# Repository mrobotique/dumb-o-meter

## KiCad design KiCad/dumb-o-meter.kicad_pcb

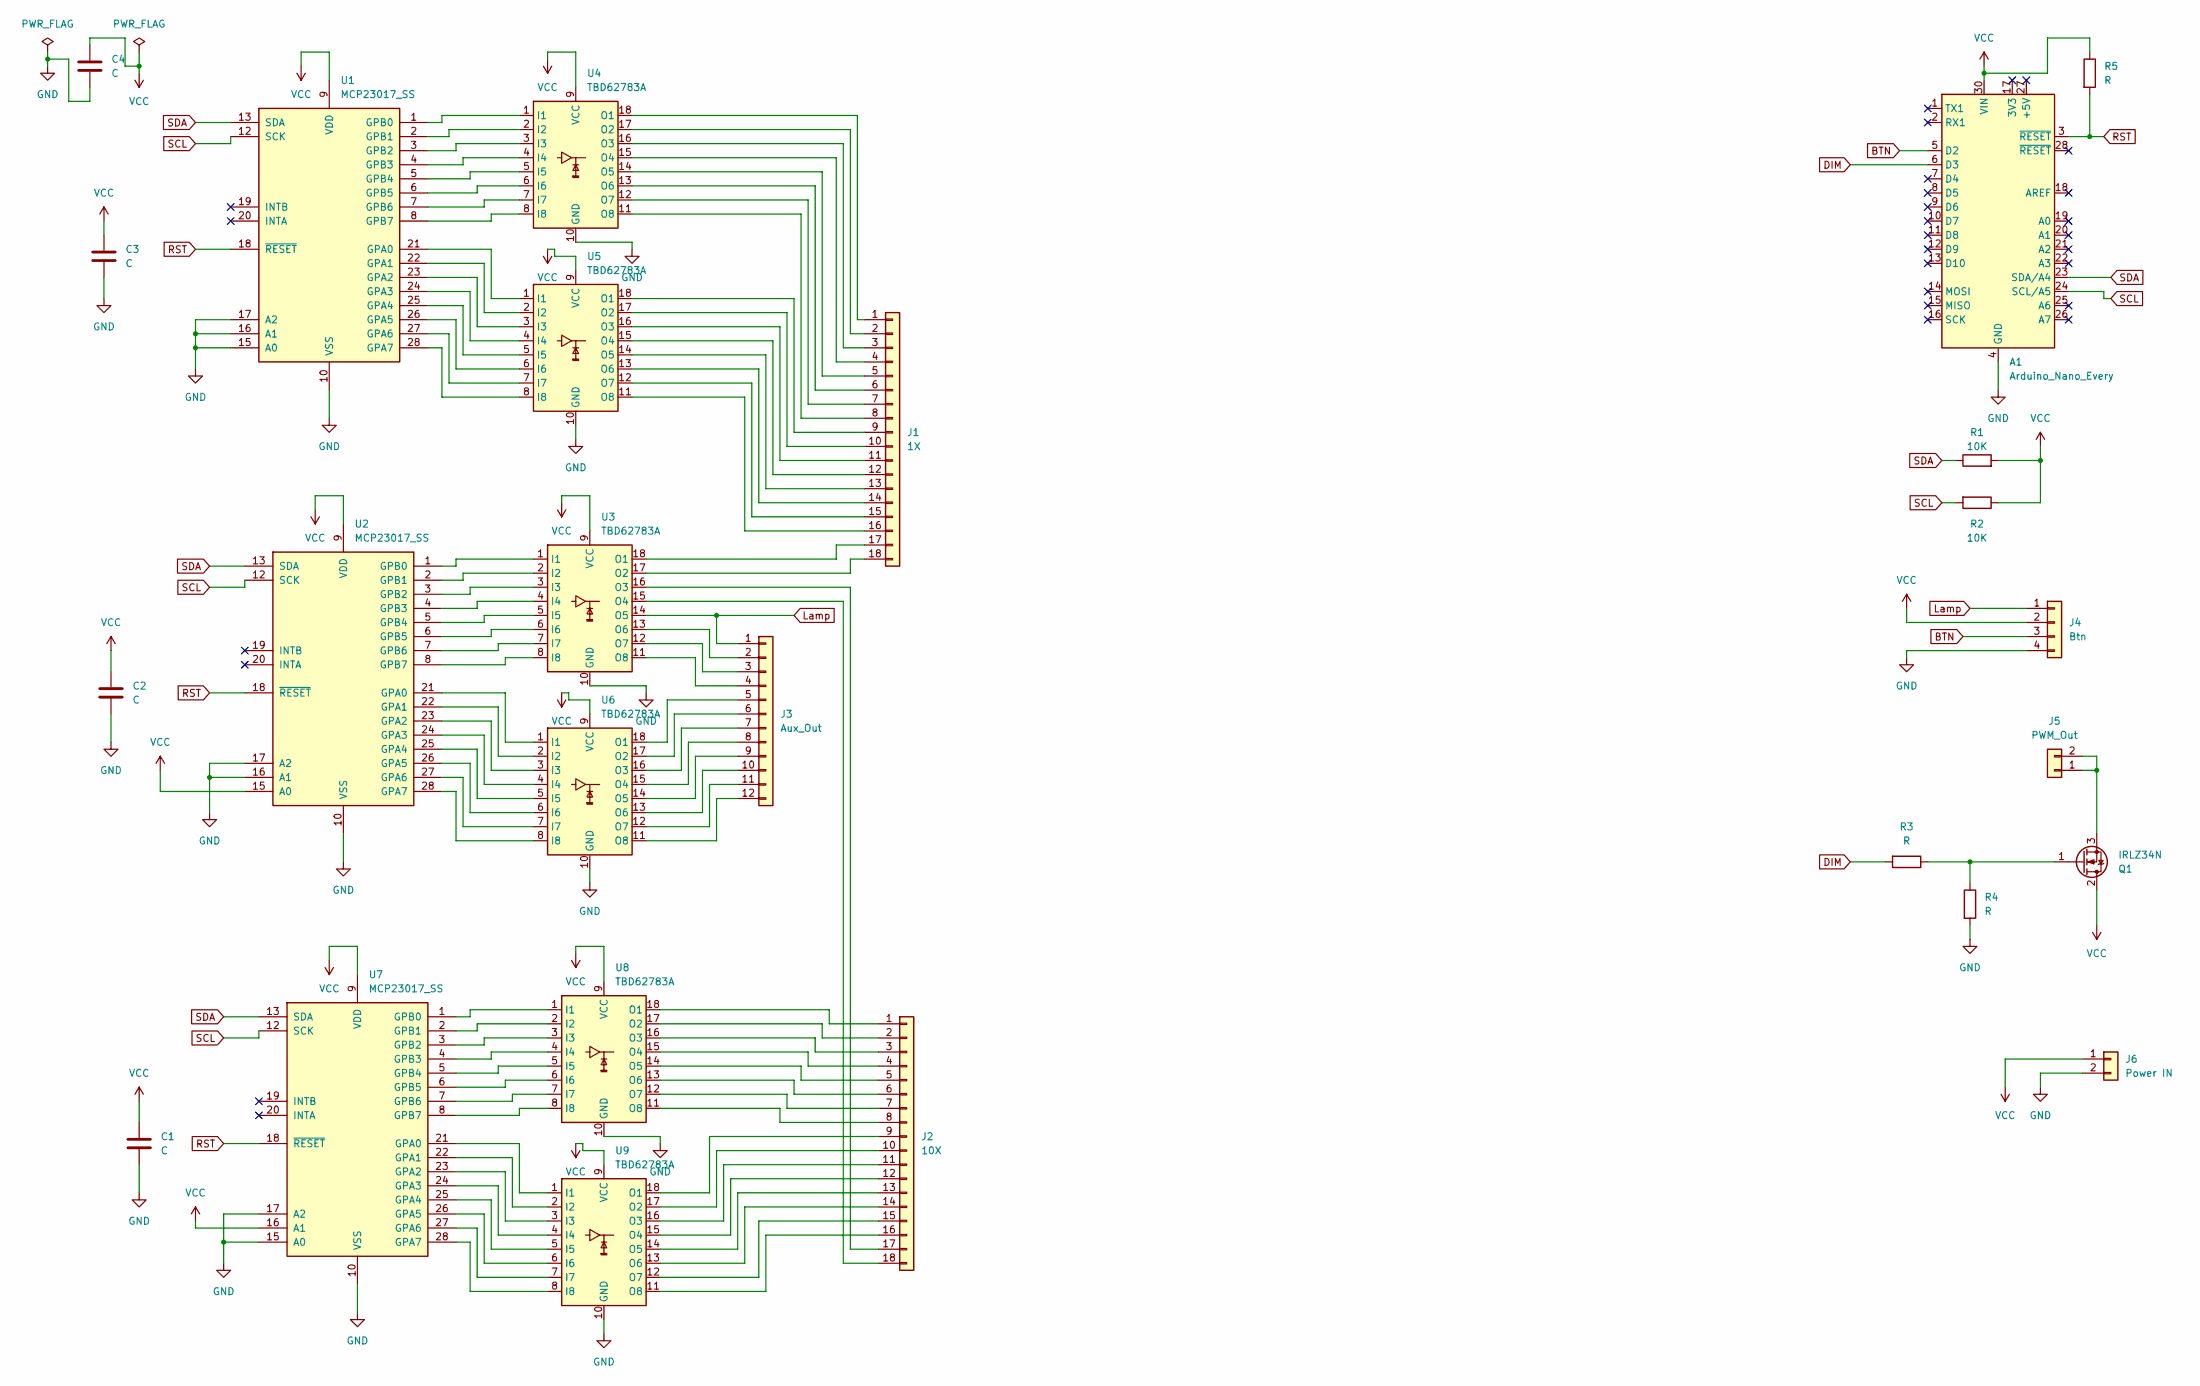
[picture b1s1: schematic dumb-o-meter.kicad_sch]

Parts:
A1: Arduino_Nano_Every; Arduino_Nano
C1, C2, C3: C; C_01005_0402Metric_Pad0.57x0.30mm_HandSolder
C4: C; CP_EIA-7343-15_Kemet-W_Pad2.25x2.55mm_HandSolder
J1: 1X; Wago_734-178_1x18_P3.50mm_Horizontal
J2: 10X; Wago_734-178_1x18_P3.50mm_Horizontal
J3: Aux_Out; PinHeader_1x12_P2.54mm_Vertical
J4: Btn; PinHeader_1x04_P2.54mm_Vertical
J5: PWM_Out; Wago_734-132_1x02_P3.50mm_Vertical
J6: Power IN; Wago_734-132_1x02_P3.50mm_Vertical
Q1: IRLZ34N; TO-263-3_TabPin2
R1, R2: 10K; R_0805_2012Metric_Pad1.20x1.40mm_HandSolder
R3, R4, R5: R; R_0805_2012Metric_Pad1.20x1.40mm_HandSolder
U1, U2, U7: MCP23017_SS; SSOP-28_5.3x10.2mm_P0.65mm
U3, U4, U5, U6, U8, U9: TBD62783A; SOIC-18W_7.5x11.6mm_P1.27mm

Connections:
BTN: A1.5 (D2), J4.3
DIM: A1.6 (D3), R3.2
GND: A1.4 (GND), A1.29 (GND), C1.2, C2.2, C3.2, C4.2, J4.4, J6.2, R4.2, U1.10 (VSS), U1.15 (A0), U1.16 (A1), U1.17 (A2), U2.10 (VSS), U2.16 (A1), U2.17 (A2), U3.10 (GND), U4.10 (GND), U5.10 (GND), U6.10 (GND), U7.10 (VSS), U7.15 (A0), U7.17 (A2), U8.10 (GND), U9.10 (GND)
Lamp: J3.1, J4.1, U3.14 (O5)
unnamed: J1.1, U4.18 (O1)
unnamed: J1.2, U4.17 (O2)
unnamed: J1.3, U4.16 (O3)
unnamed: J1.4, U4.15 (O4)
unnamed: J1.5, U4.14 (O5)
unnamed: J1.6, U4.13 (O6)
unnamed: J1.7, U4.12 (O7)
unnamed: J1.8, U4.11 (O8)
unnamed: J1.9, U5.18 (O1)
unnamed: J1.10, U5.17 (O2)
unnamed: J1.11, U5.16 (O3)
unnamed: J1.12, U5.15 (O4)
unnamed: J1.13, U5.14 (O5)
unnamed: J1.14, U5.13 (O6)
unnamed: J1.15, U5.12 (O7)
unnamed: J1.16, U5.11 (O8)
unnamed: J1.17, U3.18 (O1)
unnamed: J1.18, U3.17 (O2)
unnamed: J2.1, U8.18 (O1)
unnamed: J2.2, U8.17 (O2)
unnamed: J2.3, U8.16 (O3)
unnamed: J2.4, U8.15 (O4)
unnamed: J2.5, U8.14 (O5)
unnamed: J2.6, U8.13 (O6)
unnamed: J2.7, U8.12 (O7)
unnamed: J2.8, U8.11 (O8)
unnamed: J2.9, U9.18 (O1)
unnamed: J2.10, U9.17 (O2)
unnamed: J2.11, U9.16 (O3)
unnamed: J2.12, U9.15 (O4)
unnamed: J2.13, U9.14 (O5)
unnamed: J2.14, U9.13 (O6)
unnamed: J2.15, U9.12 (O7)
unnamed: J2.16, U9.11 (O8)
unnamed: J2.17, U3.16 (O3)
unnamed: J2.18, U3.15 (O4)
unnamed: J3.2, U3.13 (O6)
unnamed: J3.3, U3.12 (O7)
unnamed: J3.4, U3.11 (O8)
unnamed: J3.5, U6.18 (O1)
unnamed: J3.6, U6.17 (O2)
unnamed: J3.7, U6.16 (O3)
unnamed: J3.8, U6.15 (O4)
unnamed: J3.9, U6.14 (O5)
unnamed: J3.10, U6.13 (O6)
unnamed: J3.11, U6.12 (O7)
unnamed: J3.12, U6.11 (O8)
unnamed: J5.1, J5.2, Q1.3 (S)
unnamed: Q1.1 (G), R3.1, R4.1
unnamed: U1.21 (GPA0), U5.1 (I1)
unnamed: U1.22 (GPA1), U5.2 (I2)
unnamed: U1.23 (GPA2), U5.3 (I3)
unnamed: U1.24 (GPA3), U5.4 (I4)
unnamed: U1.25 (GPA4), U5.5 (I5)
unnamed: U1.26 (GPA5), U5.6 (I6)
unnamed: U1.27 (GPA6), U5.7 (I7)
unnamed: U1.28 (GPA7), U5.8 (I8)
unnamed: U1.1 (GPB0), U4.1 (I1)
unnamed: U1.2 (GPB1), U4.2 (I2)
unnamed: U1.3 (GPB2), U4.3 (I3)
unnamed: U1.4 (GPB3), U4.4 (I4)
unnamed: U1.5 (GPB4), U4.5 (I5)
unnamed: U1.6 (GPB5), U4.6 (I6)
unnamed: U1.7 (GPB6), U4.7 (I7)
unnamed: U1.8 (GPB7), U4.8 (I8)
unnamed: U2.21 (GPA0), U6.1 (I1)
unnamed: U2.22 (GPA1), U6.2 (I2)
unnamed: U2.23 (GPA2), U6.3 (I3)
unnamed: U2.24 (GPA3), U6.4 (I4)
unnamed: U2.25 (GPA4), U6.5 (I5)
unnamed: U2.26 (GPA5), U6.6 (I6)
unnamed: U2.27 (GPA6), U6.7 (I7)
unnamed: U2.28 (GPA7), U6.8 (I8)
unnamed: U2.1 (GPB0), U3.1 (I1)
unnamed: U2.2 (GPB1), U3.2 (I2)
unnamed: U2.3 (GPB2), U3.3 (I3)
unnamed: U2.4 (GPB3), U3.4 (I4)
unnamed: U2.5 (GPB4), U3.5 (I5)
unnamed: U2.6 (GPB5), U3.6 (I6)
unnamed: U2.7 (GPB6), U3.7 (I7)
unnamed: U2.8 (GPB7), U3.8 (I8)
unnamed: U7.21 (GPA0), U9.1 (I1)
unnamed: U7.22 (GPA1), U9.2 (I2)
unnamed: U7.23 (GPA2), U9.3 (I3)
unnamed: U7.24 (GPA3), U9.4 (I4)
unnamed: U7.25 (GPA4), U9.5 (I5)
unnamed: U7.26 (GPA5), U9.6 (I6)
unnamed: U7.27 (GPA6), U9.7 (I7)
unnamed: U7.28 (GPA7), U9.8 (I8)
unnamed: U7.1 (GPB0), U8.1 (I1)
unnamed: U7.2 (GPB1), U8.2 (I2)
unnamed: U7.3 (GPB2), U8.3 (I3)
unnamed: U7.4 (GPB3), U8.4 (I4)
unnamed: U7.5 (GPB4), U8.5 (I5)
unnamed: U7.6 (GPB5), U8.6 (I6)
unnamed: U7.7 (GPB6), U8.7 (I7)
unnamed: U7.8 (GPB7), U8.8 (I8)
RST: A1.3 (~RESET), R5.2, U1.18 (~RESET), U2.18 (~RESET), U7.18 (~RESET)
SCL: A1.24 (SCL/A5), R2.2, U1.12 (SCK), U2.12 (SCK), U7.12 (SCK)
SDA: A1.23 (SDA/A4), R1.1, U1.13 (SDA), U2.13 (SDA), U7.13 (SDA)
VCC: A1.30 (VIN), C1.1, C2.1, C3.1, C4.1, J4.2, J6.1, Q1.2 (D), R1.2, R2.1, R5.1, U1.9 (VDD), U2.9 (VDD), U2.15 (A0), U3.9 (VCC), U4.9 (VCC), U5.9 (VCC), U6.9 (VCC), U7.9 (VDD), U7.16 (A1), U8.9 (VCC), U9.9 (VCC)

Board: 2 copper layers, 26 parts (0 on the bottom side), 105 nets, no tracks yet.

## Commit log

2023-06-19 Code Readme
2023-06-19 Repo Readme
2023-06-19 fix wemos
2023-10-04 Update New version
2023-10-04 Readme
2023-10-04 updates local jca
2023-10-13 first release MVP
